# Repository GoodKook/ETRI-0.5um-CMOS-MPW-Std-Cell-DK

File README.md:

# ETRI 0.5um CMOS MPW Std-Cell DK
ETRI 0.5um CMOS MPW Std-Cell Design-Kit
----------------------------------------

Visit following blog page for more information,

https://fun-teaching-goodkook.blogspot.com/2024/07/mpw.html

Join MyChip Open-Source Design Kit User Group,

https://groups.google.com/g/mychip-on-mydesk

* Note: Blog page is written in Korean. You may read via machine translation.

Installation
------------

Change to tool installation script folder,

    cd ./Tools

Install Pre-requisitive packages,

    ./prerequisites.sh

Run script to download, build and install basic required tools,

    ./build_tools.sh

Or each tool separately.

Yosys, RTL synthesizer, https://github.com/YosysHQ

    ./yosys_build.sh
    
GrayWolf, Auto-Placer, https://github.com/rubund/graywolf

    ./graywolf_build.sh

QRouter, Auto-Router, https://github.com/RTimothyEdwards/qrouter

    ./qrouter_build.sh

Magic, VLSI layout editor, https://github.com/RTimothyEdwards/magic

    ./magic_build.sh

iRSim, switch level simulator, https://github.com/RTimothyEdwards/irsim

    ./irsim_build.sh

KLayout, layout tool, https://www.klayout.de/

    ./klayout_install.sh
    
Netgen, LVS & LVL Netlist compare, https://github.com/RTimothyEdwards/netgen

    ./netgen_build.sh

QFlow with ETRI050 tech., https://github.com/RTimothyEdwards/qflow

    ./qflow-1.4.100_etri050_build.sh

ngSpice, SPICE circuit simulator, https://ngspice.sourceforge.io/

    ./ngspice42_build.sh

XSchem, schematic entry, https://xschem.sourceforge.io/stefan/index.html

    ./xschem_build.sh

iVerilog, Verilog Simulator, https://github.com/steveicarus/iverilog

    ./iverilog_build.sh

SystemC, C++ class library for system level simulation & modeling, https://systemc.org/

    ./systemc_build.sh
    
Verilator, Verilog to SystemC/C++ converter, https://www.veripool.org/verilator/

    ./verilator_build.sh

gtkWave, digital waveform viewer, https://gtkwave.sourceforge.net/

    ./gtkwave_install.sh

Example/Reference Design
------------------------
The example includes synthesis, P&R, layout generation, LVS and RTL simulation at system-level using Verilated SystemC testbench.

1. Symbolic link Download(cloned) directory to "~/ETRI050_DesignKit"

        ln -s ETRI-0.5um-CMOS-MPW-Std-Cell-DK ~/ETRI050_DesignKit

2. goto example directory,

        cd ~/ETRI050_DesignKit/Tutorials/2-6_Lab4_FIR_PE

3. Make Std-Cell Libs.

        make config_m1f

4. Make Synthesize,

        make synthesize

5. Make Place & Route,

        make place; make route

6. Make migrate & LVS,

        make migrate; make lvs

Have fun!

Kook, goodkook(at)gmail.com

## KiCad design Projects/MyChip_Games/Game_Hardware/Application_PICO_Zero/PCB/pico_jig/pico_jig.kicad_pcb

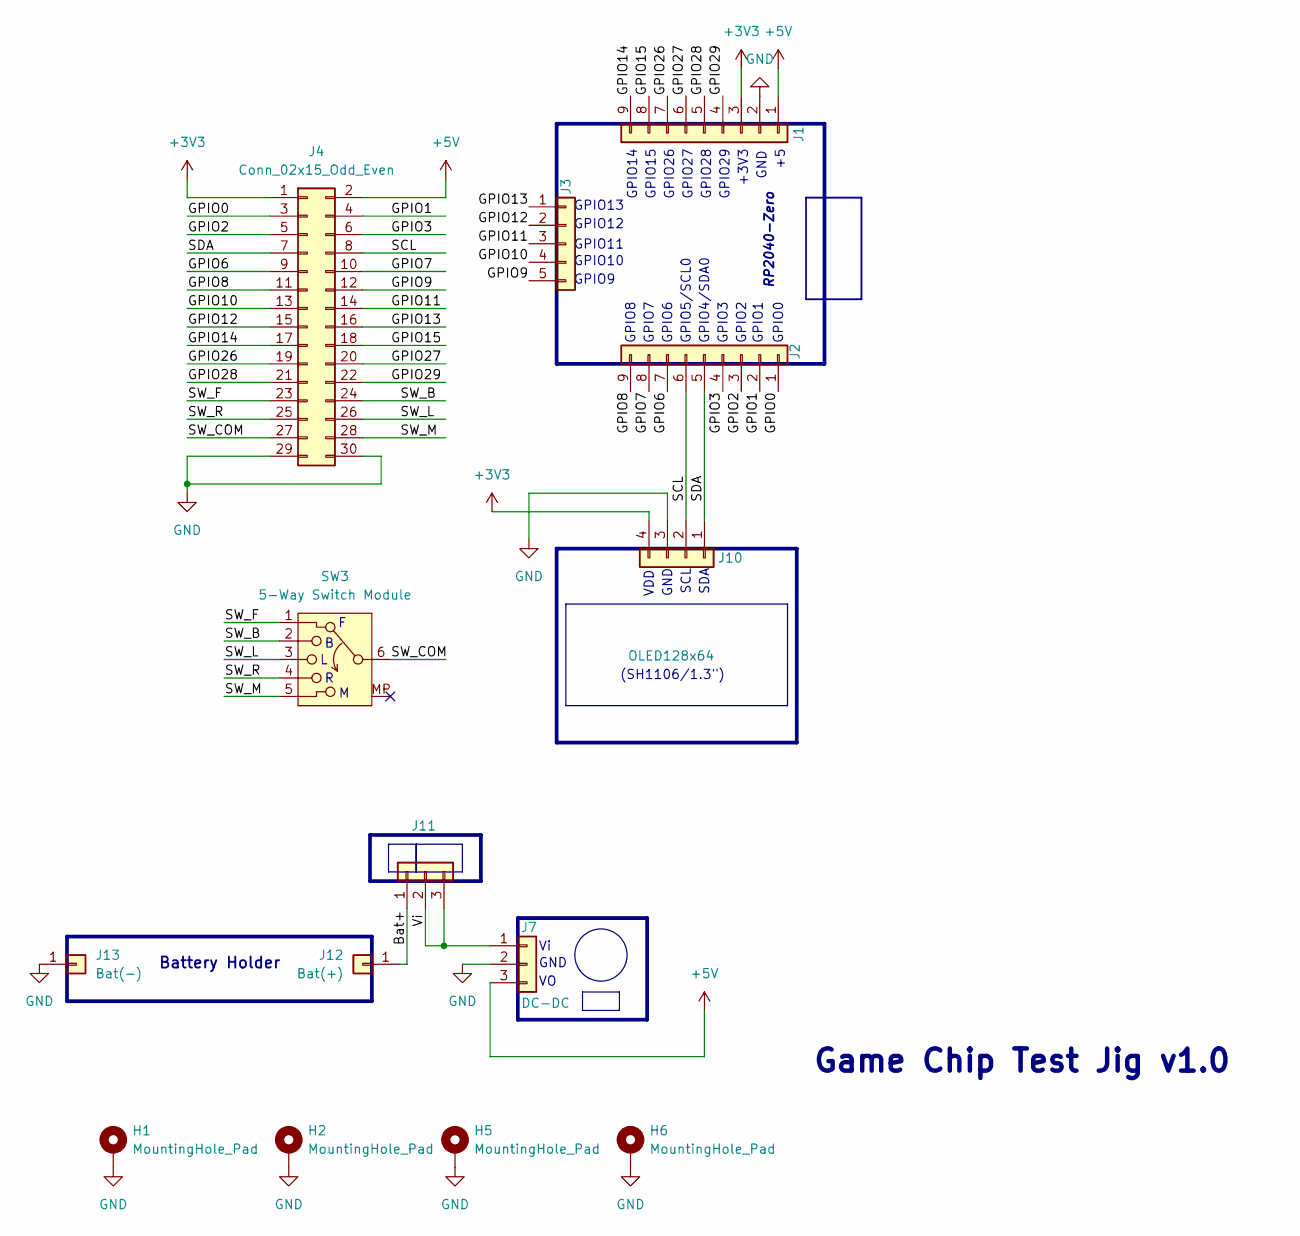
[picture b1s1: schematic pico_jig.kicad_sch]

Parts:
H1, H2, H5, H6: MountingHole_Pad; MountingHole_3.2mm_M3_DIN965_Pad
J1: RP_L; PinHeader_1x09_P2.54mm_Vertical
J2: RP_R; PinHeader_1x09_P2.54mm_Vertical
J3: RP_B; PinHeader_1x05_P2.54mm_Vertical
J4: Conn_02x15_Odd_Even; PinHeader_2x15_P2.54mm_Vertical
J7: DC-DC; PinHeader_1x03_P2.54mm_Vertical
J10: OLED128x64; PinHeader_1x04_P2.54mm_Vertical
J11: pwr_sw; PinHeader_1x03_P2.54mm_Vertical
J12: Bat(+); PinHeader_1x01_P2.54mm_Vertical
J13: Bat(-); PinHeader_1x01_P2.54mm_Vertical
SW3: 5-Way Switch Module; PinHeader_1x06_P2.54mm_Vertical

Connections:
+3V3: J1.3, J4.1, J10.4
+5V: J1.1, J4.2, J7.3
/Bat+: J11.1, J12.1 (Pin_1_1)
/GPIO0: J2.1, J4.3
/GPIO1: J2.2, J4.4
/GPIO2: J2.3, J4.5
/GPIO3: J2.4, J4.6
/GPIO6: J2.7, J4.9
/GPIO7: J2.8, J4.10
/GPIO8: J2.9, J4.11
/GPIO9: J3.5, J4.12
/GPIO10: J3.4, J4.13
/GPIO11: J3.3, J4.14
/GPIO12: J3.2, J4.15
/GPIO13: J3.1, J4.16
/GPIO14: J1.9, J4.17
/GPIO15: J1.8, J4.18
/GPIO26: J1.7, J4.19
/GPIO27: J1.6, J4.20
/GPIO28: J1.5, J4.21
/GPIO29: J1.4, J4.22
/SCL: J2.6, J4.8, J10.2
/SDA: J2.5, J4.7, J10.1
/SW_B: J4.24, SW3.2
/SW_COM: J4.27, SW3.6
/SW_F: J4.23, SW3.1
/SW_L: J4.26, SW3.3
/SW_M: J4.28, SW3.5
/SW_R: J4.25, SW3.4
/Vi: J7.1, J11.2, J11.3
GND: H1.1 (1_1), H2.1 (1_1), H5.1 (1_1), H6.1 (1_1), J1.2, J4.29, J4.30, J7.2, J10.3, J13.1 (Pin_1_1)

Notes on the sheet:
GND
GPIO9
GPIO13
SDA
GPIO15
GPIO8
GPIO5/SCL0
GPIO27
GPIO6
GPIO26
GPIO11
+3V3
RP2040-Zero
VDD
(SH1106/1.3")
GPIO3
GPIO2
Game Chip Test Jig v1.0
GPIO12
GPIO14
GPIO28
GPIO7
GPIO0
GPIO10
GPIO4/SDA0
GPIO29
SCL
GPIO1
Battery Holder

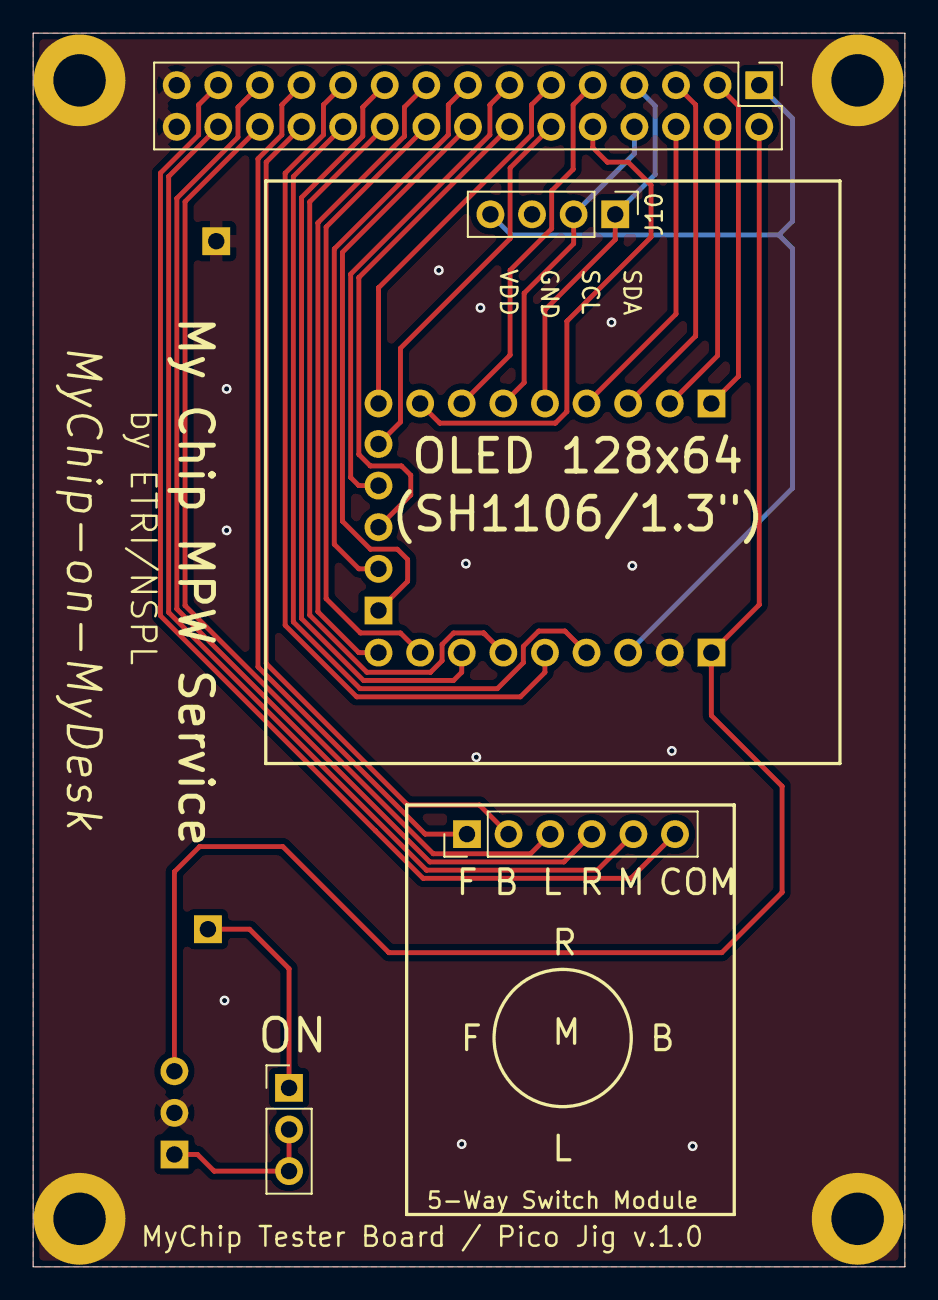
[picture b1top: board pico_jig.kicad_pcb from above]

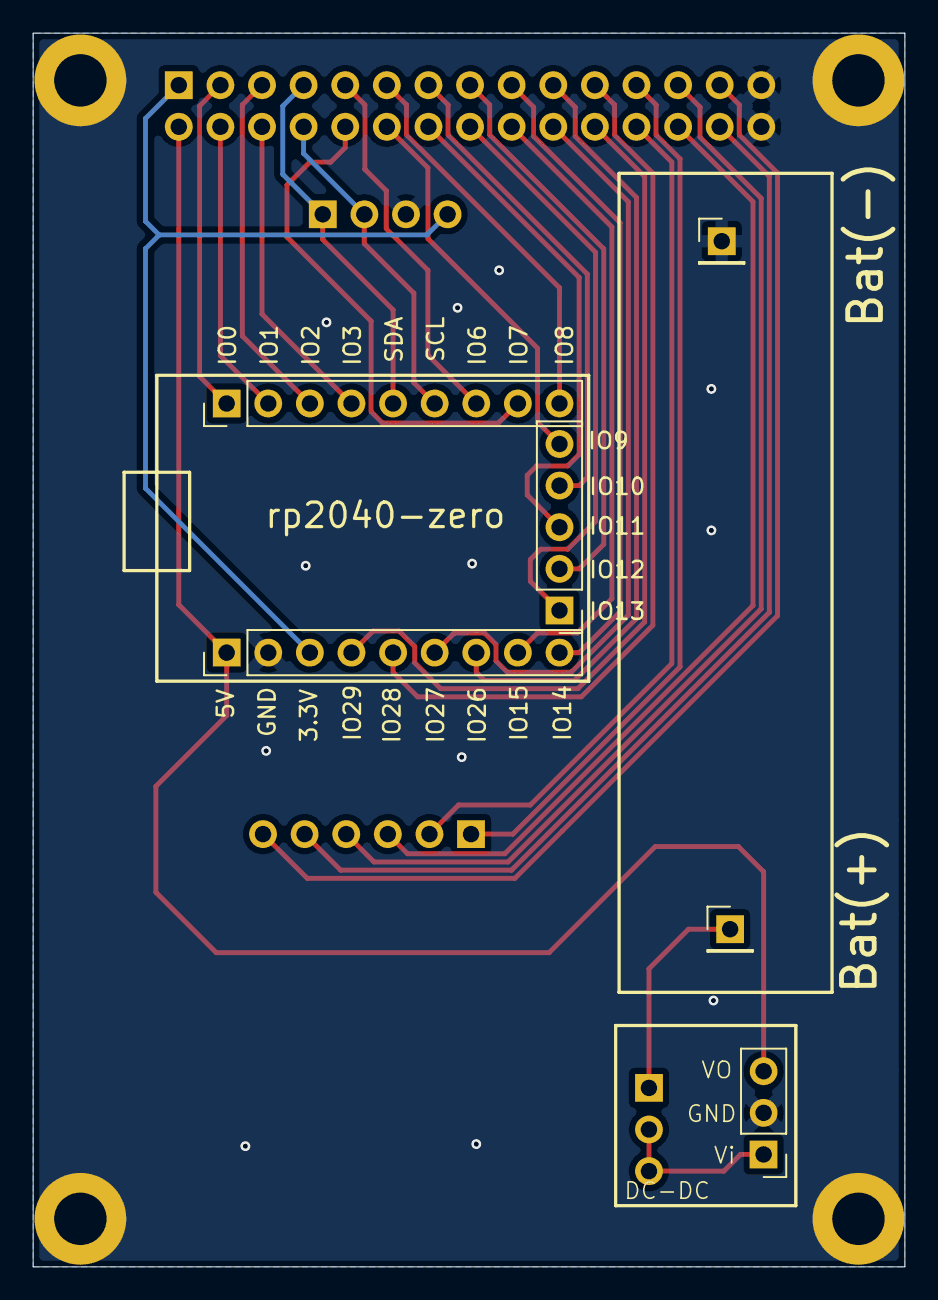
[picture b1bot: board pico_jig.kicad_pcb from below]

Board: 2 copper layers, 53.2 x 75.3 mm, 14 parts (6 on the bottom side), 31 nets.

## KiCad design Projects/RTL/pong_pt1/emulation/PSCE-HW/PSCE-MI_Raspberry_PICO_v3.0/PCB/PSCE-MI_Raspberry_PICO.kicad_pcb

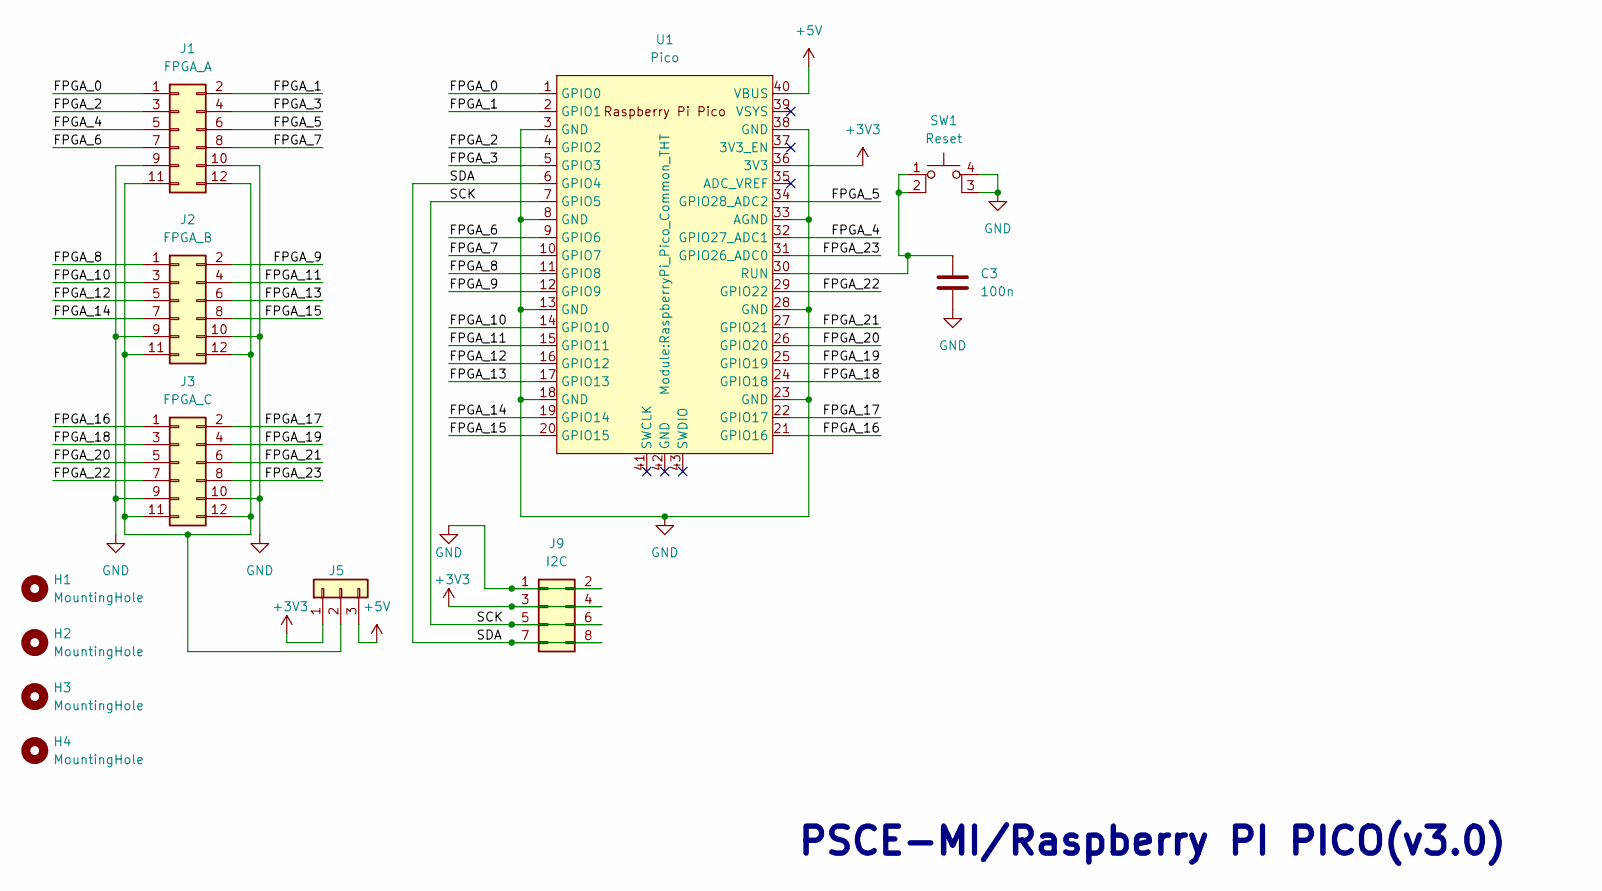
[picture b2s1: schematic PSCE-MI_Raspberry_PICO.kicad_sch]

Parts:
C3: 100n; C_Disc_D3.8mm_W2.6mm_P2.50mm
H1, H2, H3, H4: MountingHole; MountingHole_3.2mm_M3_DIN965_Pad
J1: FPGA_A; PinHeader_2x06_P2.54mm_Vertical
J2: FPGA_B; PinHeader_2x06_P2.54mm_Vertical
J3: FPGA_C; PinHeader_2x06_P2.54mm_Vertical
J5: Conn_01x03; PinHeader_1x03_P2.54mm_Vertical
J9: I2C; PinHeader_2x04_P2.54mm_Vertical
SW1: Reset; SW_PUSH_6mm_H9.5mm
U1: Pico; RaspberryPi_Pico_Common_THT

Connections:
+3V3: J5.1, J9.3, J9.4, U1.36 (3V3)
+5V: J5.3, U1.40 (VBUS)
/FPGA_0: J1.1, U1.1 (GPIO0)
/FPGA_1: J1.2, U1.2 (GPIO1)
/FPGA_2: J1.3, U1.4 (GPIO2)
/FPGA_3: J1.4, U1.5 (GPIO3)
/FPGA_4: J1.5, U1.32 (GPIO27_ADC1)
/FPGA_5: J1.6, U1.34 (GPIO28_ADC2)
/FPGA_6: J1.7, U1.9 (GPIO6)
/FPGA_7: J1.8, U1.10 (GPIO7)
/FPGA_8: J2.1, U1.11 (GPIO8)
/FPGA_9: J2.2, U1.12 (GPIO9)
/FPGA_10: J2.3, U1.14 (GPIO10)
/FPGA_11: J2.4, U1.15 (GPIO11)
/FPGA_12: J2.5, U1.16 (GPIO12)
/FPGA_13: J2.6, U1.17 (GPIO13)
/FPGA_14: J2.7, U1.19 (GPIO14)
/FPGA_15: J2.8, U1.20 (GPIO15)
/FPGA_16: J3.1, U1.21 (GPIO16)
/FPGA_17: J3.2, U1.22 (GPIO17)
/FPGA_18: J3.3, U1.24 (GPIO18)
/FPGA_19: J3.4, U1.25 (GPIO19)
/FPGA_20: J3.5, U1.26 (GPIO20)
/FPGA_21: J3.6, U1.27 (GPIO21)
/FPGA_22: J3.7, U1.29 (GPIO22)
/FPGA_23: J3.8, U1.31 (GPIO26_ADC0)
/SCK: J9.5, J9.6, U1.7 (GPIO5)
/SDA: J9.7, J9.8, U1.6 (GPIO4)
GND: C3.2, J1.9, J1.10, J2.9, J2.10, J3.9, J3.10, J9.1, J9.2, SW1.3 (K), SW1.4 (A), U1.3 (GND), U1.8 (GND), U1.13 (GND), U1.18 (GND), U1.23 (GND), U1.28 (GND), U1.33 (AGND), U1.38 (GND)
unnamed: J1.11, J1.12, J2.11, J2.12, J3.11, J3.12, J5.2
unnamed: C3.1, SW1.1, SW1.2, U1.30 (RUN)

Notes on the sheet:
PSCE-MI/Raspberry PI PICO(v3.0)

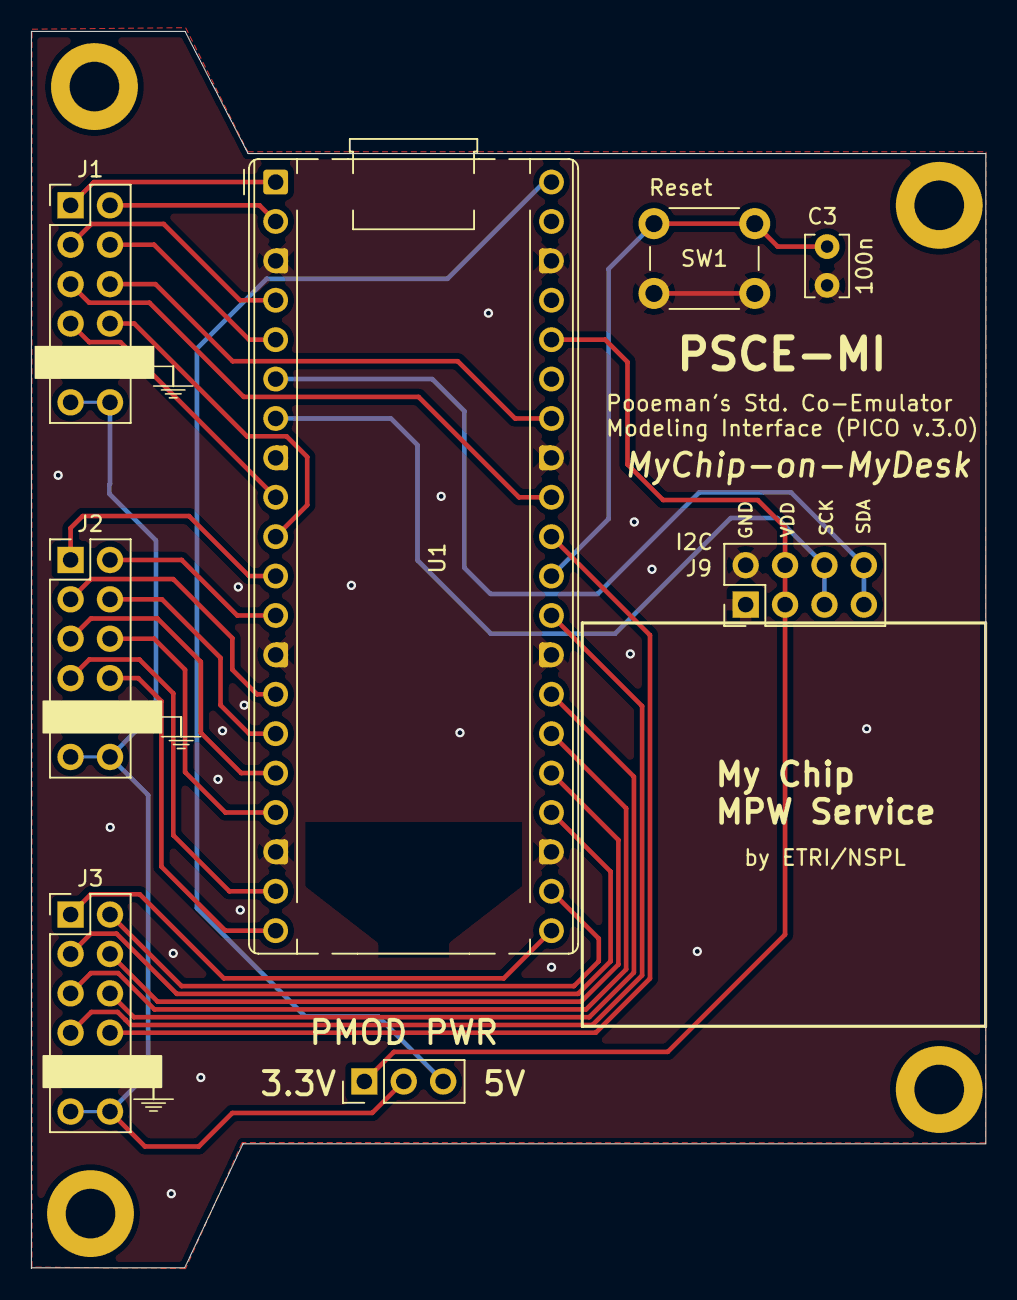
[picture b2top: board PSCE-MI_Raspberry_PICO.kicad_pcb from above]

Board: 2 copper layers, 61.5 x 79.8 mm, 12 parts (0 on the bottom side), 31 nets.

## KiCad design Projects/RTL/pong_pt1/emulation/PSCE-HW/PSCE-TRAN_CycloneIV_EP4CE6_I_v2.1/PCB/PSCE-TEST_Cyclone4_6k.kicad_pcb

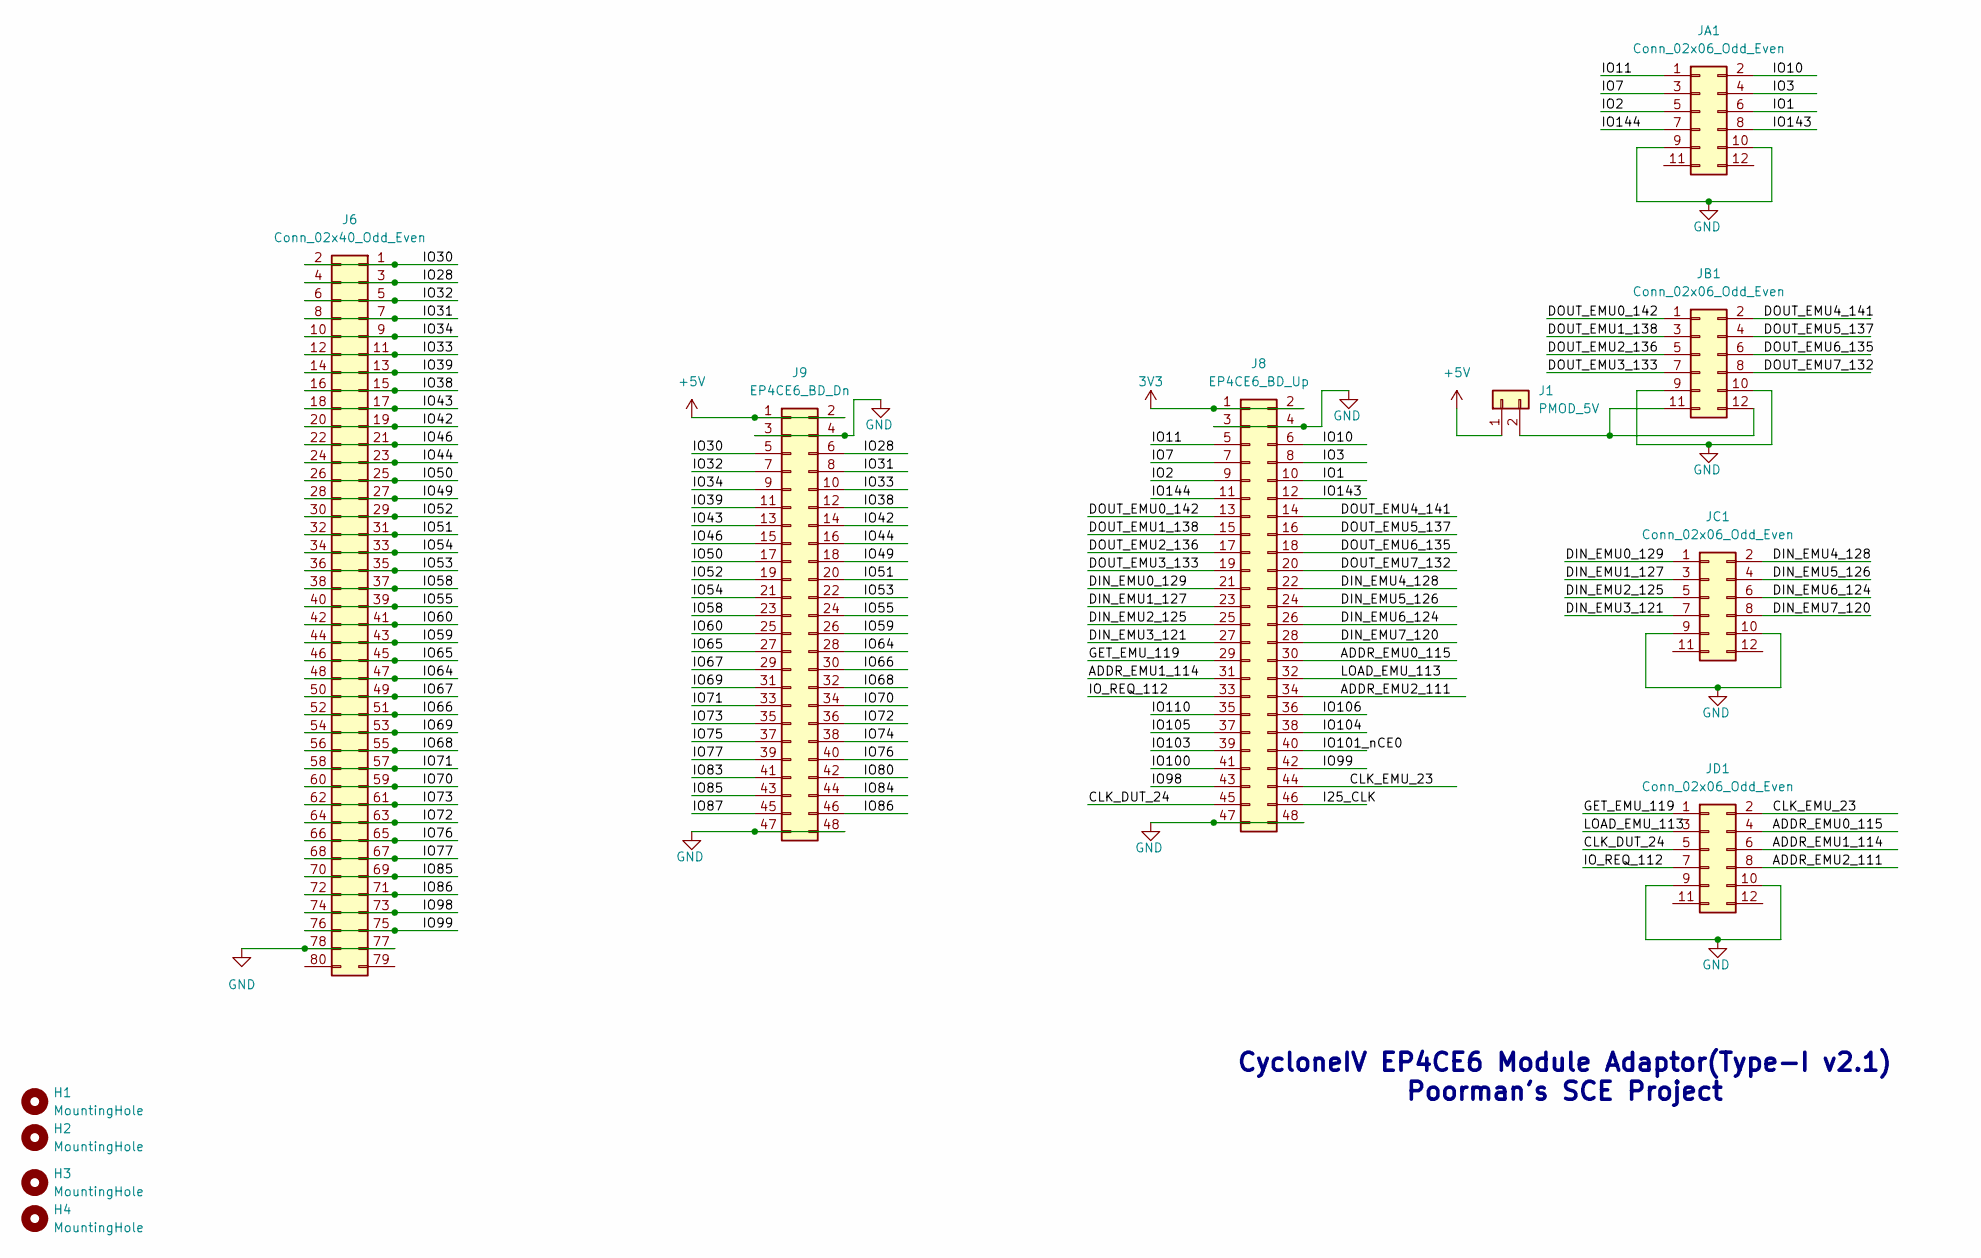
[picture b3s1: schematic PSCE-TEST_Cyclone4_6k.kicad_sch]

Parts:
H1, H2, H3, H4: MountingHole; MountingHole_3.5mm
J1: PMOD_5V; PinHeader_1x02_P2.54mm_Vertical
J6: Conn_02x40_Odd_Even; PinHeader_2x40_P2.54mm_Vertical
J8: EP4CE6_BD_Up; PinHeader_2x24_P2.54mm_Vertical
J9: EP4CE6_BD_Dn; PinHeader_2x24_P2.54mm_Vertical
JA1: Conn_02x06_Odd_Even; PinHeader_2x06_P2.54mm_Vertical
JB1: Conn_02x06_Odd_Even; PinHeader_2x06_P2.54mm_Vertical
JC1: Conn_02x06_Odd_Even; PinHeader_2x06_P2.54mm_Vertical
JD1: Conn_02x06_Odd_Even; PinHeader_2x06_P2.54mm_Vertical

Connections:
3V3: J8.1, J8.2
+5V: J1.1, J9.1, J9.2
/ADDR_EMU0_115: J8.30, JD1.4
/ADDR_EMU1_114: J8.31, JD1.6
/ADDR_EMU2_111: J8.34, JD1.8
/CLK_DUT_24: J8.45, JD1.5
/CLK_EMU_23: J8.44, JD1.2
/DIN_EMU0_129: J8.21, JC1.1
/DIN_EMU1_127: J8.23, JC1.3
/DIN_EMU2_125: J8.25, JC1.5
/DIN_EMU3_121: J8.27, JC1.7
/DIN_EMU4_128: J8.22, JC1.2
/DIN_EMU5_126: J8.24, JC1.4
/DIN_EMU6_124: J8.26, JC1.6
/DIN_EMU7_120: J8.28, JC1.8
/DOUT_EMU0_142: J8.13, JB1.1
/DOUT_EMU1_138: J8.15, JB1.3
/DOUT_EMU2_136: J8.17, JB1.5
/DOUT_EMU3_133: J8.19, JB1.7
/DOUT_EMU4_141: J8.14, JB1.2
/DOUT_EMU5_137: J8.16, JB1.4
/DOUT_EMU6_135: J8.18, JB1.6
/DOUT_EMU7_132: J8.20, JB1.8
/GET_EMU_119: J8.29, JD1.1
/I25_CLK: J8.46
/IO1: J8.10, JA1.6
/IO2: J8.9, JA1.5
/IO3: J8.8, JA1.4
/IO7: J8.7, JA1.3
/IO10: J8.6, JA1.2
/IO11: J8.5, JA1.1
/IO28: J6.3, J6.4, J9.6
/IO30: J6.1, J6.2, J9.5
/IO31: J6.7, J6.8, J9.8
/IO32: J6.5, J6.6, J9.7
/IO33: J6.11, J6.12, J9.10
/IO34: J6.9, J6.10, J9.9
/IO38: J6.15, J6.16, J9.12
/IO39: J6.13, J6.14, J9.11
/IO42: J6.19, J6.20, J9.14
/IO43: J6.17, J6.18, J9.13
/IO44: J6.23, J6.24, J9.16
/IO46: J6.21, J6.22, J9.15
/IO49: J6.27, J6.28, J9.18
/IO50: J6.25, J6.26, J9.17
/IO51: J6.31, J6.32, J9.20
/IO52: J6.29, J6.30, J9.19
/IO53: J6.35, J6.36, J9.22
/IO54: J6.33, J6.34, J9.21
/IO55: J6.39, J6.40, J9.24
/IO58: J6.37, J6.38, J9.23
/IO59: J6.43, J6.44, J9.26
/IO60: J6.41, J6.42, J9.25
/IO64: J6.47, J6.48, J9.28
/IO65: J6.45, J6.46, J9.27
/IO66: J6.51, J6.52, J9.30
/IO67: J6.49, J6.50, J9.29
/IO68: J6.55, J6.56, J9.32
/IO69: J6.53, J6.54, J9.31
/IO70: J6.59, J6.60, J9.34
/IO71: J6.57, J6.58, J9.33
/IO72: J6.63, J6.64, J9.36
/IO73: J6.61, J6.62, J9.35
/IO74: J9.38
/IO75: J9.37
/IO76: J6.65, J6.66, J9.40
/IO77: J6.67, J6.68, J9.39
/IO80: J9.42
/IO83: J9.41
/IO84: J9.44
/IO85: J6.69, J6.70, J9.43
/IO86: J6.71, J6.72, J9.46
/IO87: J9.45
/IO98: J6.73, J6.74, J8.43
/IO99: J6.75, J6.76, J8.42
/IO100: J8.41
/IO101_nCE0: J8.40
/IO103: J8.39
/IO104: J8.38
/IO105: J8.37
/IO106: J8.36
/IO110: J8.35
/IO143: J8.12, JA1.8
/IO144: J8.11, JA1.7
/IO_REQ_112: J8.33, JD1.7
/LOAD_EMU_113: J8.32, JD1.3
GND: J6.77, J6.78, J8.3, J8.4, J8.47, J8.48, J9.3, J9.4, J9.47, J9.48, JA1.9, JA1.10, JB1.9, JB1.10, JC1.9, JC1.10, JD1.9, JD1.10
unnamed: J1.2, JB1.11, JB1.12

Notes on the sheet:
CycloneIV EP4CE6 Module Adaptor(Type-I v2.1) Poorman's SCE Project

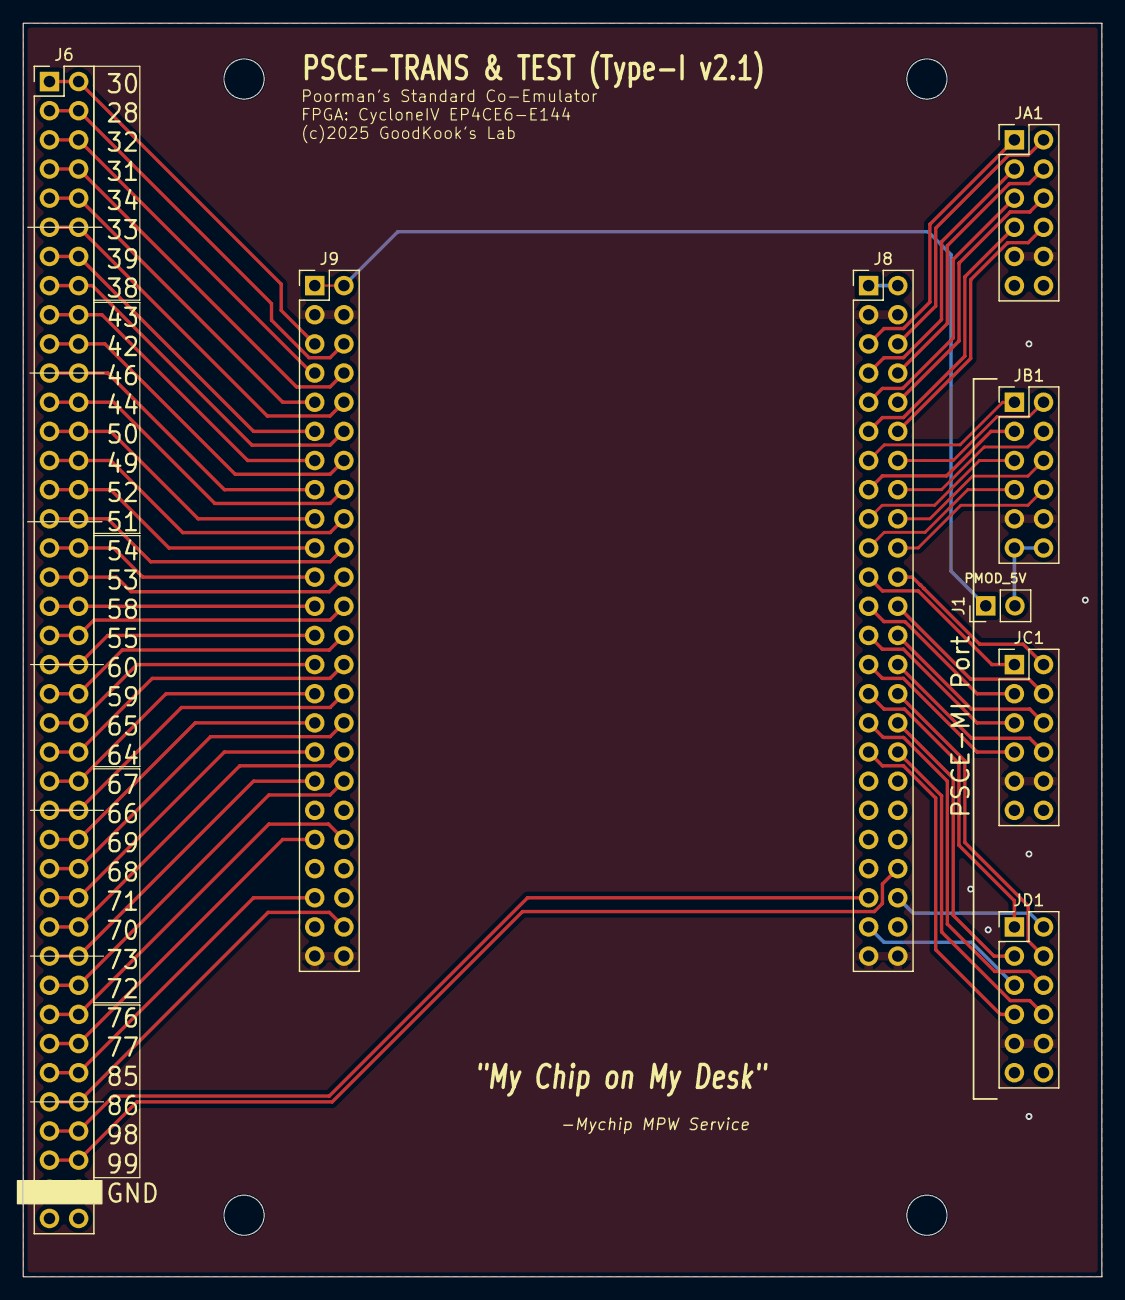
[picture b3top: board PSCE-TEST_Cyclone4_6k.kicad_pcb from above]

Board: 2 copper layers, 94.0 x 109.2 mm, 12 parts (0 on the bottom side), 74 nets.

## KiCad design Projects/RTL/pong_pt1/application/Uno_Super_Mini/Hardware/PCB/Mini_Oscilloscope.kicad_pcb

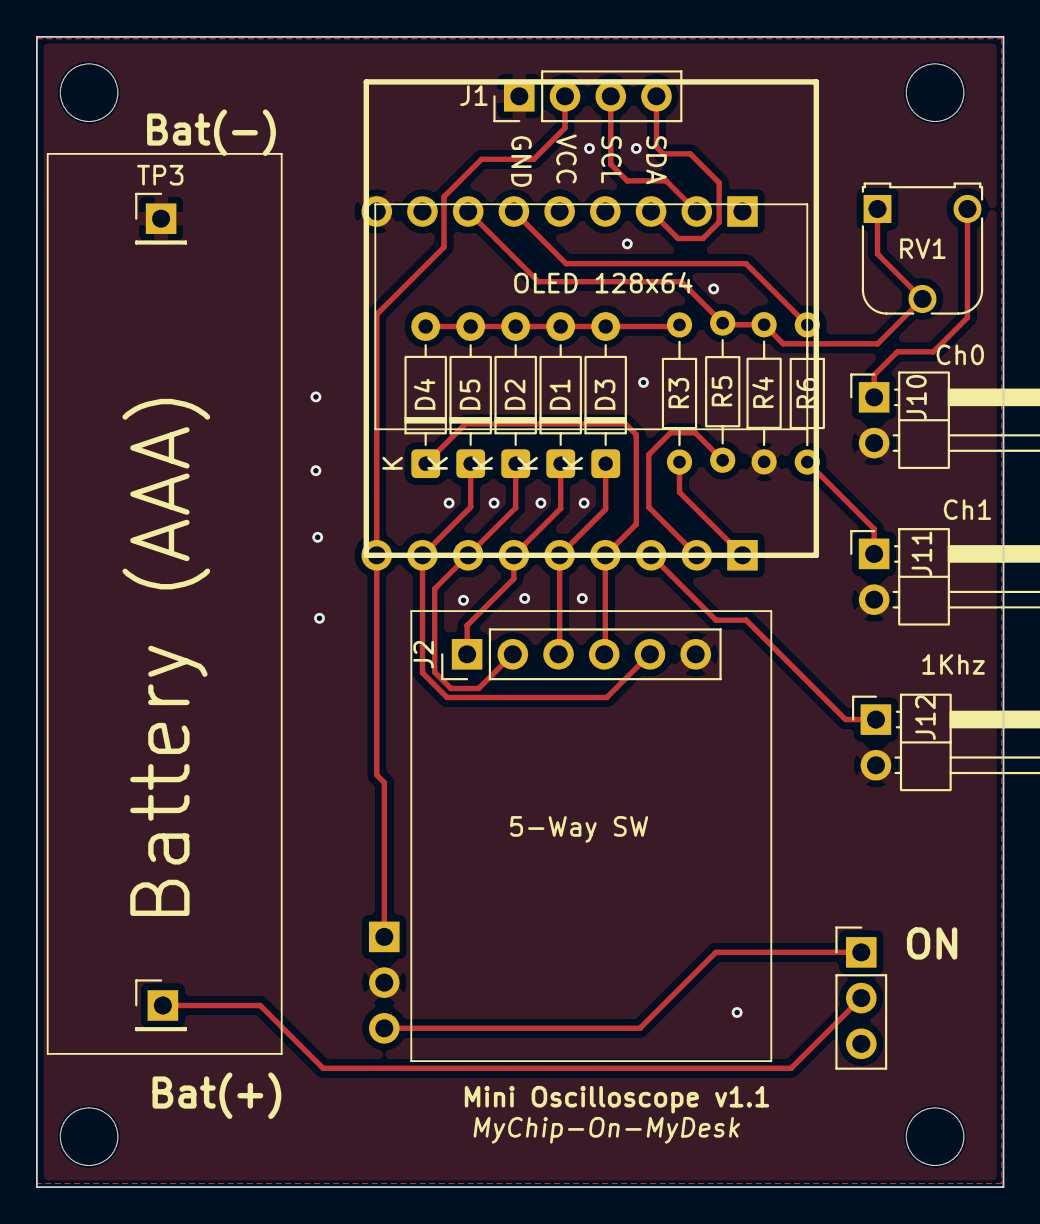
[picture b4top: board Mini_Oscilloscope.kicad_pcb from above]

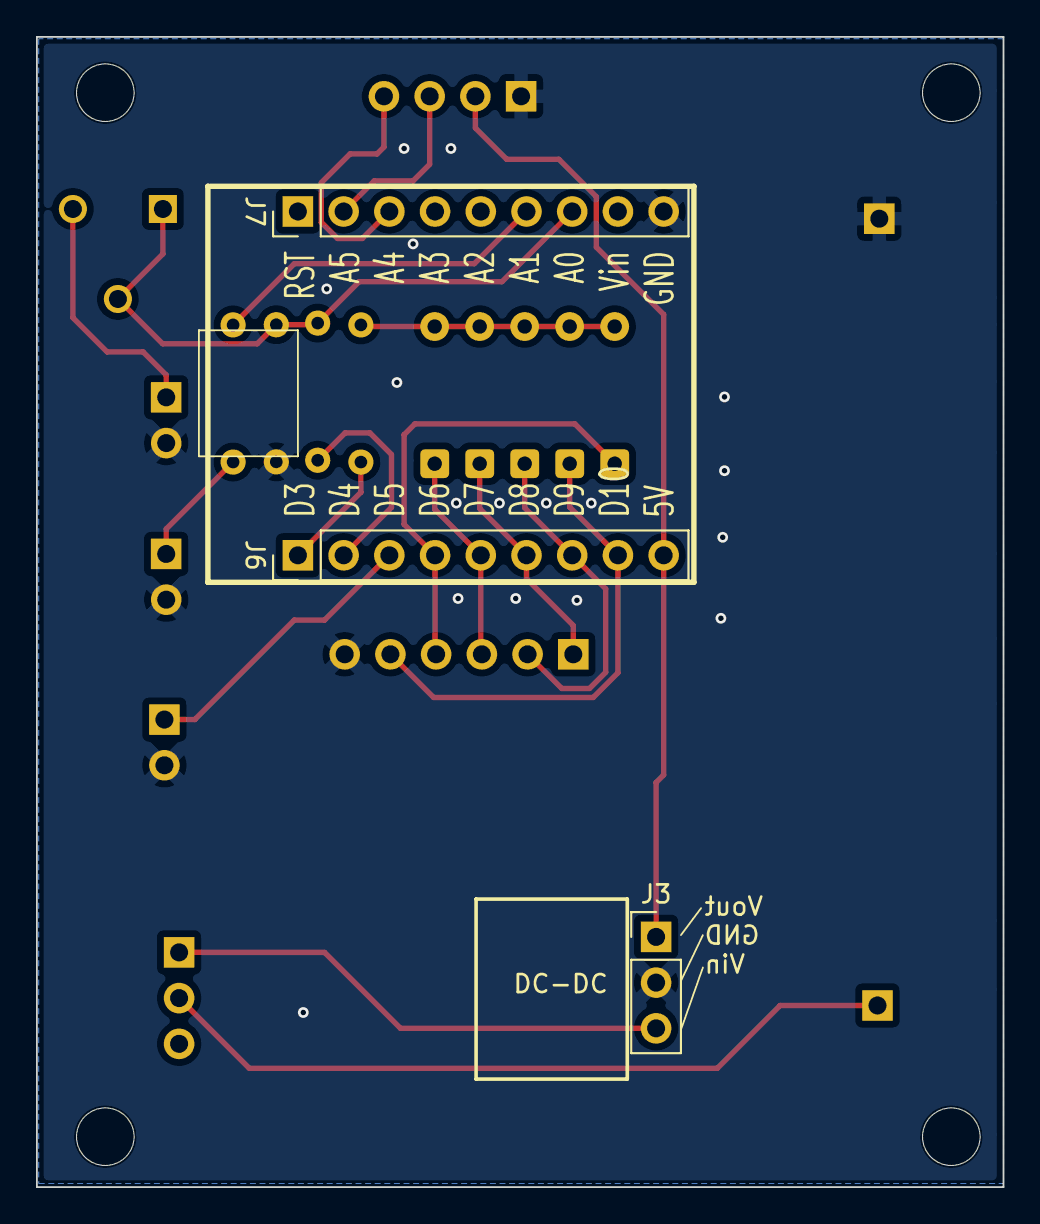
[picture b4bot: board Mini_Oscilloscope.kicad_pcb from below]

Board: 2 copper layers, 53.7 x 63.9 mm, 25 parts (3 on the bottom side), 19 nets.

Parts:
D1, D2, D3, D4, D5: 1N4148; D_DO-35_SOD27_P7.62mm_Horizontal
H1, H2, H3, H4: MountingHole_Pad; MountingHole_3.2mm_M3_DIN965
J1: OLED_128x64; PinHeader_1x04_P2.54mm_Vertical
J2: 5-Way SW; PinHeader_1x06_P2.54mm_Vertical
J3: DC-DC; PinHeader_1x03_P2.54mm_Vertical
J6: Left; PinHeader_1x09_P2.54mm_Vertical
J7: Right; PinHeader_1x09_P2.54mm_Vertical
J10: Ch0; PinHeader_1x02_P2.54mm_Horizontal
J11: Ch1; PinHeader_1x02_P2.54mm_Horizontal
J12: 1Khz; PinHeader_1x02_P2.54mm_Horizontal
R3: 10; R_Axial_DIN0204_L3.6mm_D1.6mm_P7.62mm_Horizontal
R4: 100K; R_Axial_DIN0204_L3.6mm_D1.6mm_P7.62mm_Horizontal
R5: 10K; R_Axial_DIN0204_L3.6mm_D1.6mm_P7.62mm_Horizontal
R6: 100; R_Axial_DIN0204_L3.6mm_D1.6mm_P7.62mm_Horizontal
RV1: 1M; Potentiometer_Runtron_RM-065_Vertical
SW1: SW_SPDT; PinHeader_1x03_P2.54mm_Vertical
TP2: Bat(+); PinHeader_1x01_P2.54mm_Vertical
TP3: Bat(-); PinHeader_1x01_P2.54mm_Vertical

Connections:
/ATT: J6.2, R5.2
/AUX: D5.1 (K), J2.5, J6.8
/DN: D3.1 (K), J2.3, J6.5
/HOLD: D2.1 (K), J2.2, J6.7
/IRQ1: J6.1, R3.2
/SCL: J1.3, J7.2
/SDA: J1.4, J7.3
/SEL: D1.1 (K), J2.1, J6.6
/UP: D4.1 (K), J2.4, J6.4
/VCC_5V: J1.2, J3.1, J6.9
GND: J1.1, J2.6, J3.2, J7.9, J10.2, J11.2, J12.2, R4.1, TP3.1 (1_1)
unnamed: D1.2 (A), D2.2 (A), D3.2 (A), D4.2 (A), D5.2 (A), R3.1
unnamed: J3.3, SW1.1 (A)
unnamed: J7.6, R6.1
unnamed: J7.7, R4.2, R5.1, RV1.1, RV1.2
unnamed: J10.1, RV1.3
unnamed: J11.1, R6.2
unnamed: J6.3, J12.1
unnamed: SW1.2 (B), TP2.1 (1_1)

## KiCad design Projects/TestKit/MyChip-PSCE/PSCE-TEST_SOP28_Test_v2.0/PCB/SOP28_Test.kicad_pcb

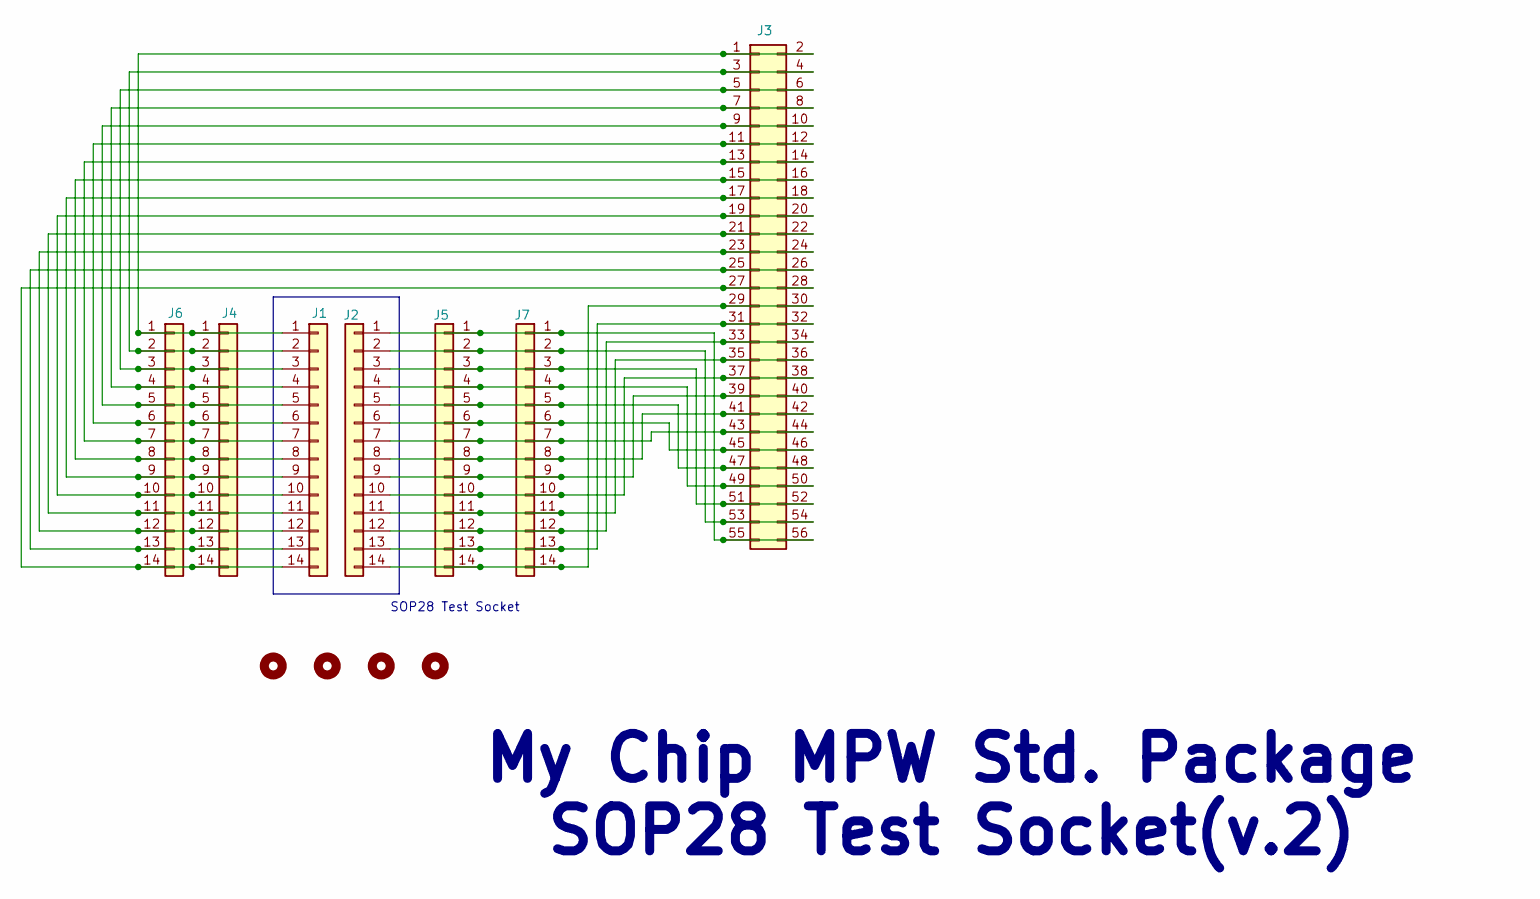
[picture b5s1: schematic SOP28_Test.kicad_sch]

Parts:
H1, H2, H3, H4: MountingHole; MountingHole_3.2mm_M3_DIN965_Pad
J1, J2, J4, J5, J6, J7: Conn_01x14; PinHeader_1x14_P2.54mm_Vertical
J3: Conn_02x28_Odd_Even; PinHeader_2x28_P2.54mm_Vertical

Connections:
unnamed: J1.1, J3.1, J3.2, J4.1, J6.1
unnamed: J1.2, J3.3, J3.4, J4.2, J6.2
unnamed: J1.3, J3.5, J3.6, J4.3, J6.3
unnamed: J1.4, J3.7, J3.8, J4.4, J6.4
unnamed: J1.5, J3.9, J3.10, J4.5, J6.5
unnamed: J1.6, J3.11, J3.12, J4.6, J6.6
unnamed: J1.7, J3.13, J3.14, J4.7, J6.7
unnamed: J1.8, J3.15, J3.16, J4.8, J6.8
unnamed: J1.9, J3.17, J3.18, J4.9, J6.9
unnamed: J1.10, J3.19, J3.20, J4.10, J6.10
unnamed: J1.11, J3.21, J3.22, J4.11, J6.11
unnamed: J1.12, J3.23, J3.24, J4.12, J6.12
unnamed: J1.13, J3.25, J3.26, J4.13, J6.13
unnamed: J1.14, J3.27, J3.28, J4.14, J6.14
unnamed: J2.1, J3.55, J3.56, J5.1, J7.1
unnamed: J2.2, J3.53, J3.54, J5.2, J7.2
unnamed: J2.3, J3.51, J3.52, J5.3, J7.3
unnamed: J2.4, J3.49, J3.50, J5.4, J7.4
unnamed: J2.5, J3.47, J3.48, J5.5, J7.5
unnamed: J2.6, J3.45, J3.46, J5.6, J7.6
unnamed: J2.7, J3.43, J3.44, J5.7, J7.7
unnamed: J2.8, J3.41, J3.42, J5.8, J7.8
unnamed: J2.9, J3.39, J3.40, J5.9, J7.9
unnamed: J2.10, J3.37, J3.38, J5.10, J7.10
unnamed: J2.11, J3.35, J3.36, J5.11, J7.11
unnamed: J2.12, J3.33, J3.34, J5.12, J7.12
unnamed: J2.13, J3.31, J3.32, J5.13, J7.13
unnamed: J2.14, J3.29, J3.30, J5.14, J7.14

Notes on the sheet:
My Chip MPW Std. Package SOP28 Test Socket(v.2)
SOP28 Test Socket

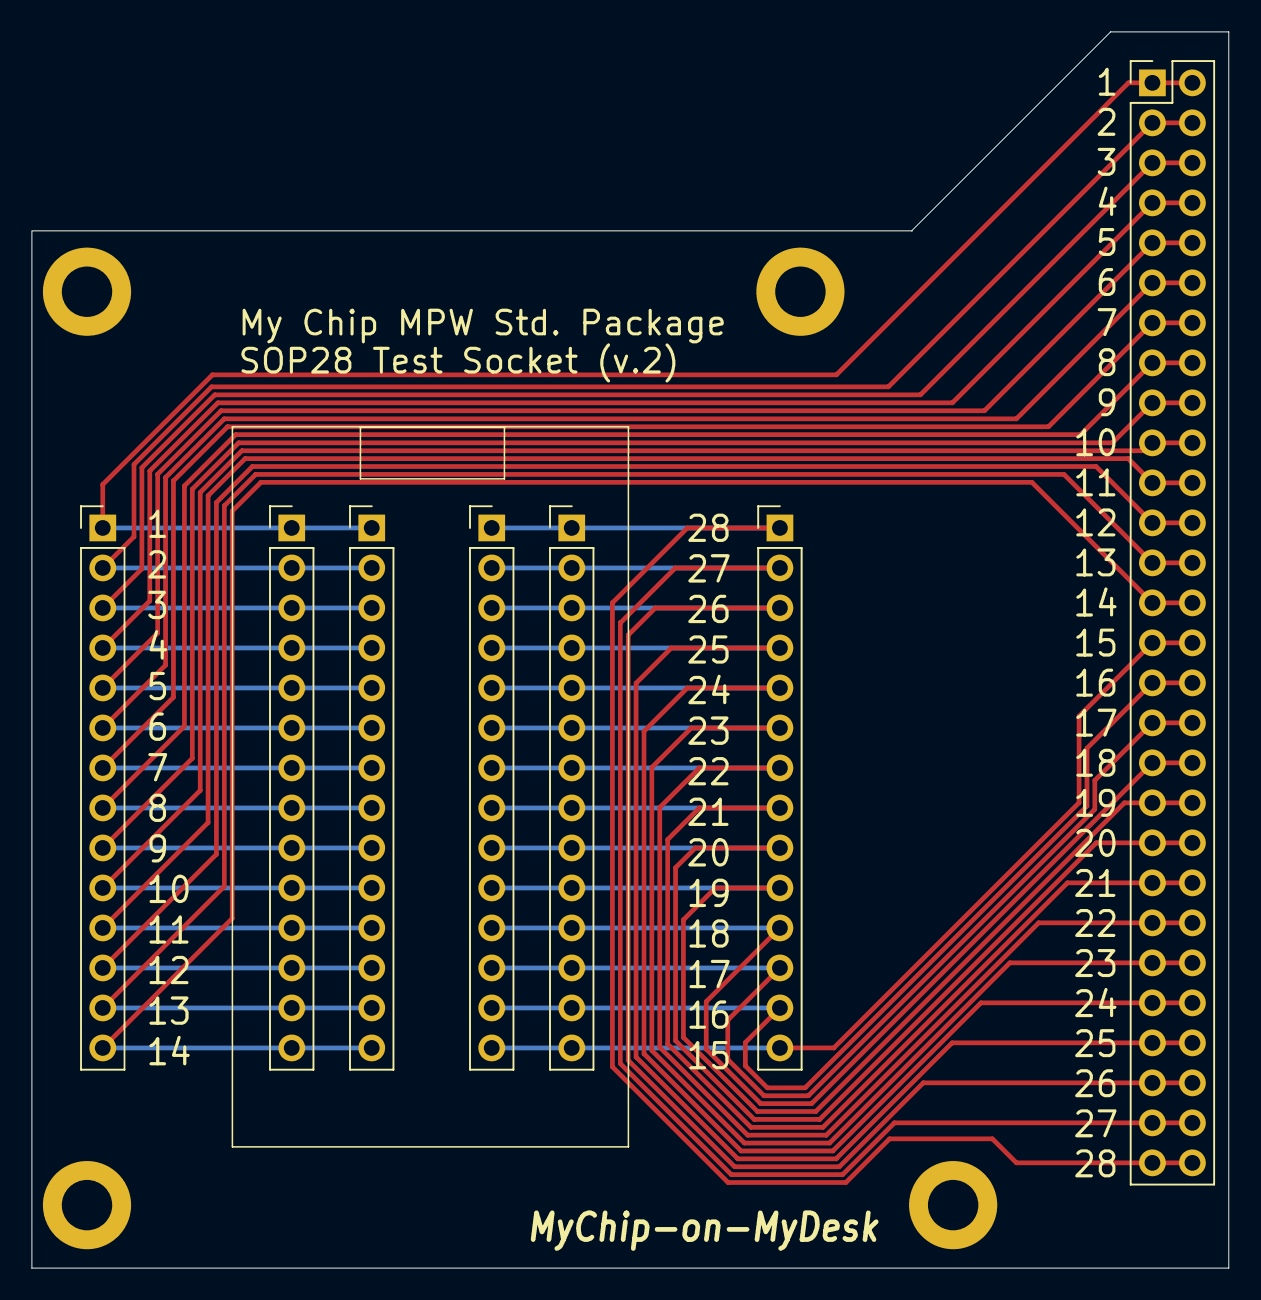
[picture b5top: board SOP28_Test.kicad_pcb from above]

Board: 2 copper layers, 76.0 x 78.5 mm, 11 parts (0 on the bottom side), 28 nets.
